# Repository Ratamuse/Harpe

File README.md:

# Harpe anti frelons à pattes jaunes

La construction de cette harpe fait suite à différents essais effectués les années passées. Montage en tubes PVC, armature en bois, bac de noyade. Ces solutions, certes peu chères, ne me satisfaisaient pas. Manque de rigidité, vieillessement prématuré, problème de cours circuits, noyades d'insectes et d'abeilles en pagaille etc etc. 
Ce montage n'est pas "LOW COST" et ne peux rivaliser avec les montages fait à partir de tréteaux, tuyaux de récupération ou autre. C'est une compilation de ce qui existe déjà, avec des améliorations et les plans sont disponibles si vous voulez en construire une.  
Ayant eu des soucis de cours circuits par le passé, j'ai ajouté un microntroleur avec capteur de luminosité et d'humidité afin de couper le montage la nuit et lorsque l'humidité est trop forte. 

Vous trouverez ci dessous les liens pour:

- [Liste du materiel](https://github.com/Ratamuse/Harpe/blob/main/Harpe%20ruches/Materiel/Materiel.md)
- [Fichier .STL pour impression 3D](https://github.com/Ratamuse/Harpe/tree/main/Harpe%20ruches%2FFichiers%203d%20%C3%A0%20imprimer)
- [Aide au montage](https://github.com/Ratamuse/Harpe/blob/main/Harpe%20ruches/Montage/Construction.md)
- [Fichiers nécessaires pour fabriquer le circuit imprimé de la harpe](https://github.com/Ratamuse/Harpe/tree/main/Harpe%20ruches/Fichier%20Kicad)
- [Exemple de montage électrique](https://github.com/Ratamuse/Harpe/blob/main/Harpe%20ruches/Fichier%20Kicad/Harpe_ESP32/PCB.md)
- [Programme pour microcontroleur ESP32](https://github.com/Ratamuse/Harpe/tree/main/Harpe%20ruches/Code%20Arduino)

** Cette harpe vous plait et est efficace. Payez moi un café! ;-) **

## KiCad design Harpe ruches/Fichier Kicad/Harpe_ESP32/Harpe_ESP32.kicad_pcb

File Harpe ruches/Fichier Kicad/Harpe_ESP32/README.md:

## Testboard V2.2 ESP32

## Carte multi-usage basée sur le module ESP-WROOM-32E:

- Connecteur USB-C

- Chargeur solaire MPPT basé sur la puce CN3791:  http://www.consonance-elec.com/pdf/datasheet/DSE-CN3791.pdf

- Connecteur batterie JST-PH 2mm avec protection (surcharge ou décharge profonde)

- Connecteur batterie JST-PH 2mm sans protection (pour batterie déjà protégée)

- Bouton on/off LTC2954 avec interrupt sur µP (On/Off de l'ESP32 et GPIO de l'interrupt utilisable pour des actions): https://www.analog.com/media/en/technical-documentation/data-sheets/2954fb.pdf

- Capteur température/humidité SHT41: https://www.sensirion.com/fileadmin/user_upload/customers/sensirion/Dokumente/2_Humidity_Sensors/Datasheets/Sensirion_Humidity_Sensors_SHT4x_Datasheet.pdf
- 10 optocoupleurs pour interrupteurs à contacts secs (pour domotiser volets roulants, télécommandes diverses) ou au choix 10 GPIO dispo avec au choix alim 3.3V ou "5V" (Vbat (entre 3.2 et 4.2V) ou Vbus (5V)) pour ajouter des modules.

- Chargeur Li-io/Li-Po MCP73831 via port USB-C

- Connecteur JST-PH 2mm (1x4) I2C

- Connecteur JST-PH 2mm (1x4) sur 2 GPIO + choix 3.3V ou 5V

- Connecteur JST-PH 2mm (1x3) sur 1 GPIO (que j'utilise pour piloter des leds neopixel)

Inspiration des travaux de Lilygo, Waveshare, GreatScoot.

Motivation et champs des possibles donnés par P. Demerliac et sa chaine Youtube Cyrob: https://www.youtube.com/channel/UC5QPFDZ3Y4ylkkGJc6Y1OOA  

Initiation à la bricole par P. W. Trainer

Prochaine étape, améliorer le hardaware du GNUVario-E

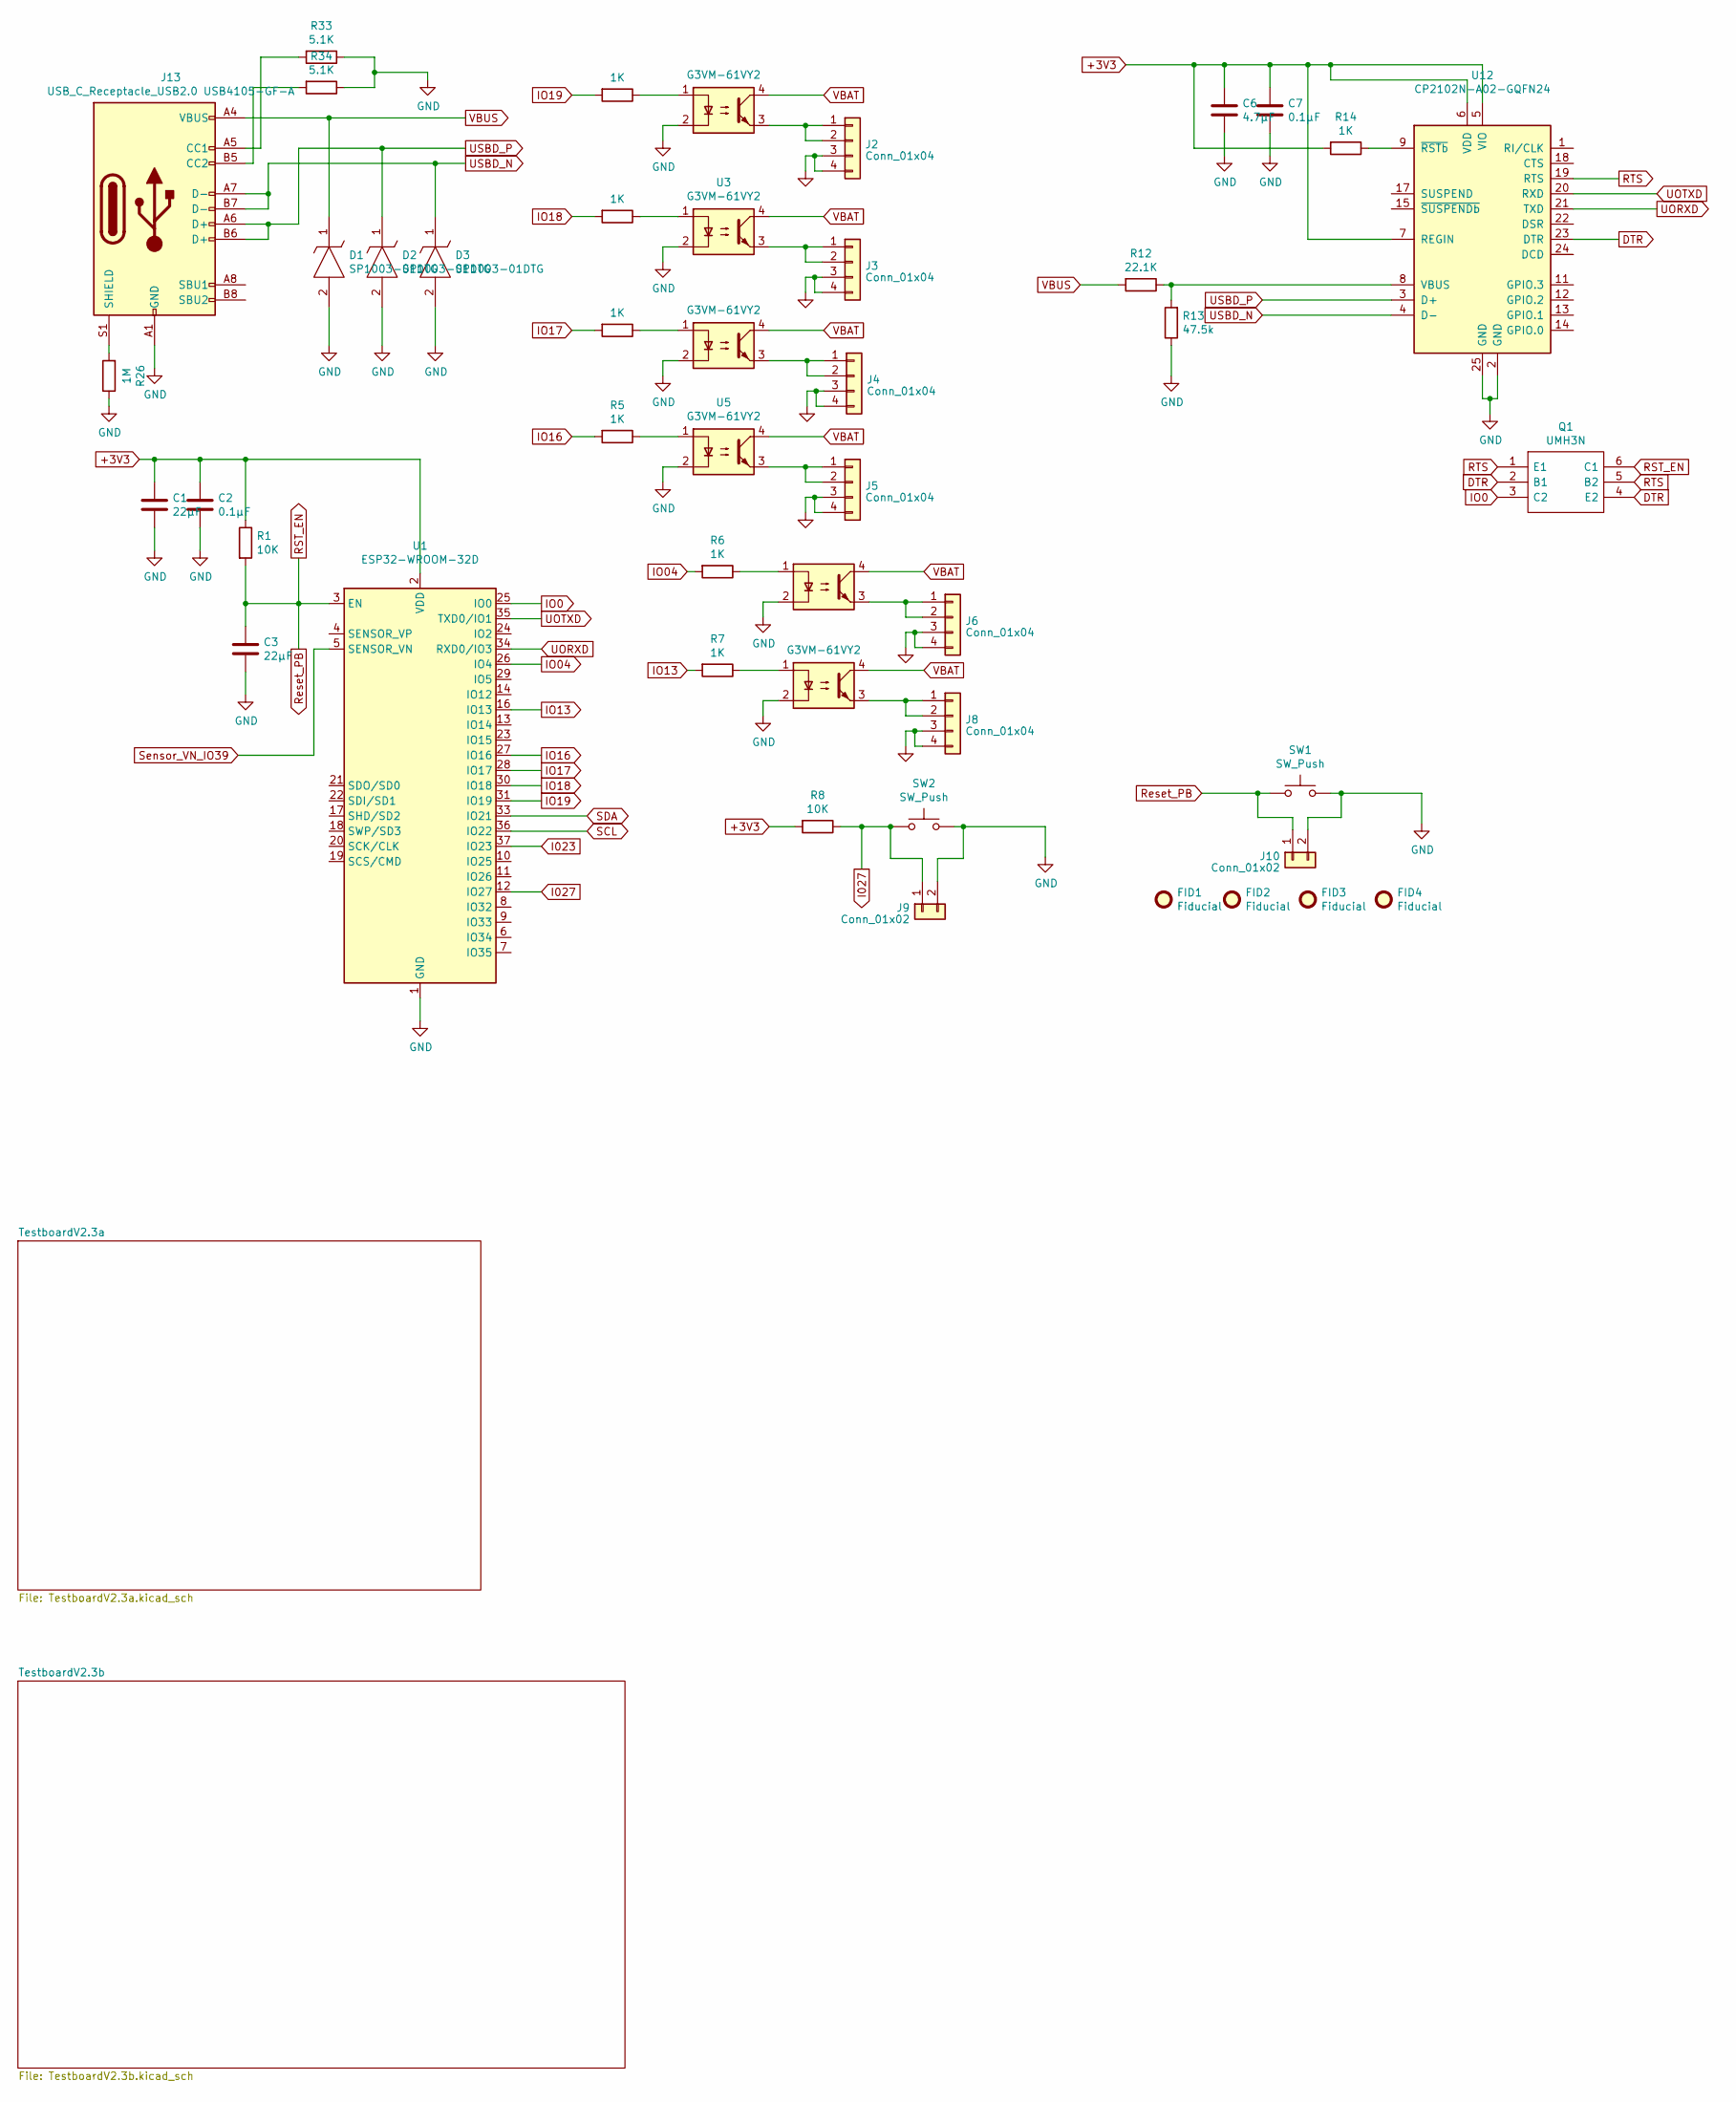
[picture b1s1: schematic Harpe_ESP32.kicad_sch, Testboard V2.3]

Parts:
C1: 22µF; 1190297
C2, C7: 0.1µF; C_0603_1608Metric
C3: 22µF; C_0805_2012Metric
C6: 4.7µF; C_0805_2012Metric
D1, D2, D3: SP1003-01DTG; SODFL1406X65N; Manufacturer_Part_Number SP1003-01DTG; Mouser Part Number 576-SP1003-01DTG
FID1, FID2, FID3, FID4: Fiducial; Fiducial_1.5mm_Mask3mm
J2, J3, J4, J5, J6, J8: Conn_01x04; 1862411
J9, J10: Conn_01x02; JST_PH_B2B-PH-K_1x02_P2.00mm_Vertical
J13: USB_C_Receptacle_USB2.0 USB4105-GF-A; TYPE-C-31-M-12
Q1: UMH3N; SOT-363_SC-70-6; Manufacturer_Part_Number UMH3N
R1, R8: 10K; R_0603_1608Metric
R2, R3, R4, R5, R6, R7, R14: 1K; R_0603_1608Metric
R12: 22.1K; R_0603_1608Metric
R13: 47.5k; R_0603_1608Metric
R26: 1M; R_0603_1608Metric
R33, R34: 5.1K; R_0603_1608Metric
SW1, SW2: SW_Push; PTS636SL43SMTRLFS
U1: ESP32-WROOM-32D; ESP32WROOM32EM113EH2800PH3Q0
U2, U3, U4, U5, U6, U7: G3VM-61VY2; SOP254P700X230-4N
U12: CP2102N-A02-GQFN24; QFN-24-1EP_4x4mm_P0.5mm_EP2.6x2.6mm

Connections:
+3V3: C1.1, C2.1, C6.1, C7.1, R1.1, R8.2, R14.2, U1.2 (VDD), U12.5 (VIO), U12.6 (VDD), U12.7 (REGIN); also elsewhere on the board
DTR: Q1.2 (B1), Q1.4 (E2), U12.23 (DTR)
I023: U1.37 (IO23)
I027: J9.1, R8.1, SW2.1, U1.12 (IO27)
IO0: Q1.3 (C2), U1.25 (IO0)
IO04: R6.2, U1.26 (IO4)
IO13: R7.2, U1.16 (IO13)
IO16: R5.2, U1.27 (IO16)
IO17: R4.2, U1.28 (IO17)
IO18: R3.2, U1.30 (IO18)
IO19: R2.2, U1.31 (IO19)
unnamed: J2.1, J2.2, U2.3
unnamed: J3.1, J3.2, U3.3
unnamed: J4.1, J4.2, U4.3
unnamed: J5.1, J5.2, U5.3
unnamed: J6.1, J6.2, U6.3
unnamed: J13.A5 (CC1), R33.2
unnamed: J13.B5 (CC2), R34.2
unnamed: J13.S1 (SHIELD), R26.2
unnamed: R2.1, U2.1
unnamed: R3.1, U3.1
unnamed: R4.1, U4.1
unnamed: R5.1, U5.1
unnamed: R6.1, U6.1
unnamed: R7.1, U7.1
unnamed: R12.1, R13.2, U12.8 (VBUS)
unnamed: R14.1, U12.9 (~RSTb)
RST_EN: C3.1, J10.1, Q1.6 (C1), R1.2, SW1.1, U1.3 (EN)
RTS: Q1.1 (E1), Q1.5 (B2), U12.19 (RTS)
SCL: U1.36 (IO22); also elsewhere on the board
SDA: U1.33 (IO21); also elsewhere on the board
Sensor_VN_IO39: U1.5 (SENSOR_VN)
UORXD: U1.34 (RXD0/IO3), U12.21 (TXD)
UOTXD: U1.35 (TXD0/IO1), U12.20 (RXD)
USBD_N: D3.1, J13.A7 (D-), J13.B7 (D-), U12.4 (D-)
USBD_P: D2.1, J13.A6 (D+), J13.B6 (D+), U12.3 (D+)
VBUS: D1.1, J13.A4 (VBUS), J13.A9 (VBUS), J13.B4 (VBUS), J13.B9 (VBUS), R12.2; also elsewhere on the board

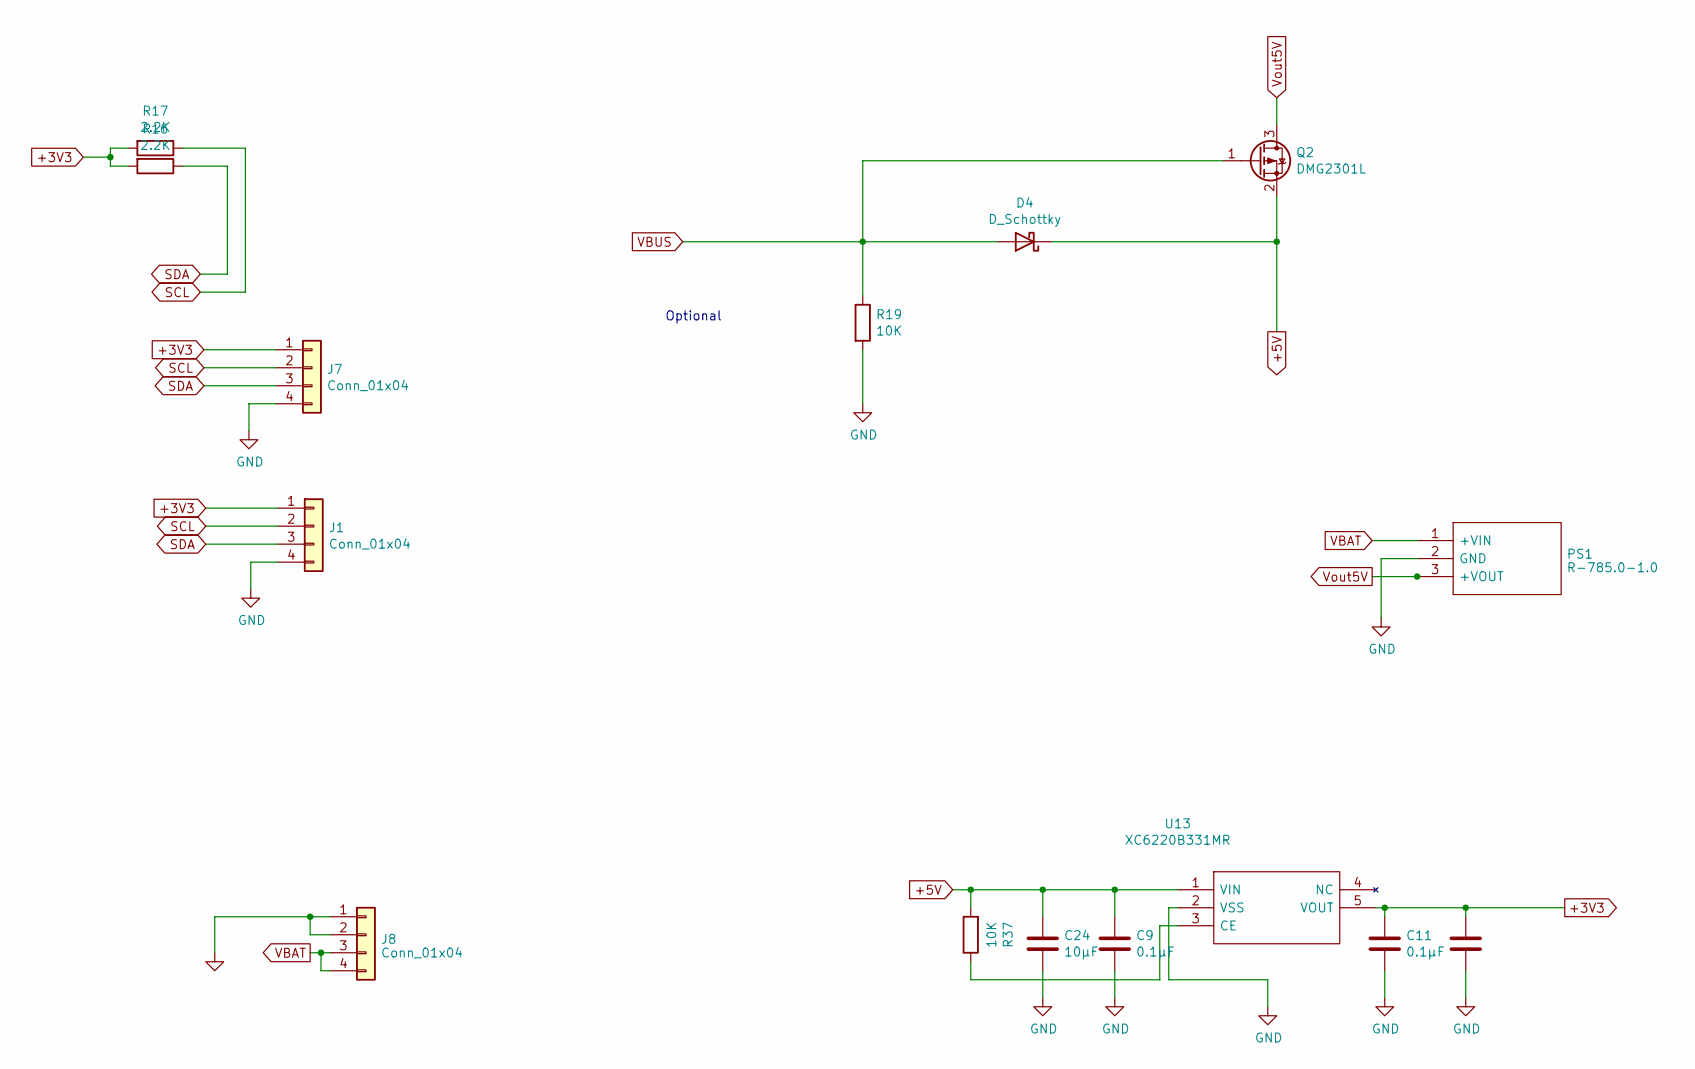
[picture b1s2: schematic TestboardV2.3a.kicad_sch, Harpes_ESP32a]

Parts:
C9, C11: 0.1µF; C_0603_1608Metric
C24, C25: 10µF; C_0805_2012Metric
D4: D_Schottky; D_SOD-323
J1, J7: Conn_01x04; 1989764
J8: Conn_01x04; 1862411
PS1: R-785.0-1.0; R785010; Mouser Part Number 919-R-785.0-1.0
Q2: DMG2301L; SOT-23
R16, R17: 2.2K; R_0603_1608Metric
R19, R37: 10K; R_0603_1608Metric
U13: XC6220B331MR; SOT-23-5

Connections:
+3V3: C11.1, C25.1, J1.1, J7.1, R16.2, R17.2, U13.5 (VOUT); also elsewhere on the board
+5V: C9.1, C24.1, D4.1 (K), Q2.2 (S), R37.2, U13.1 (VIN)
unnamed: R37.1, U13.3 (CE)
SCL: J1.2, J7.2, R17.1; also elsewhere on the board
SDA: J1.3, J7.3, R16.1; also elsewhere on the board
VBUS: D4.2 (A), Q2.1 (G), R19.1; also elsewhere on the board
Vout5V: PS1.3 (+VOUT), Q2.3 (D)

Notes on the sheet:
Optional

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
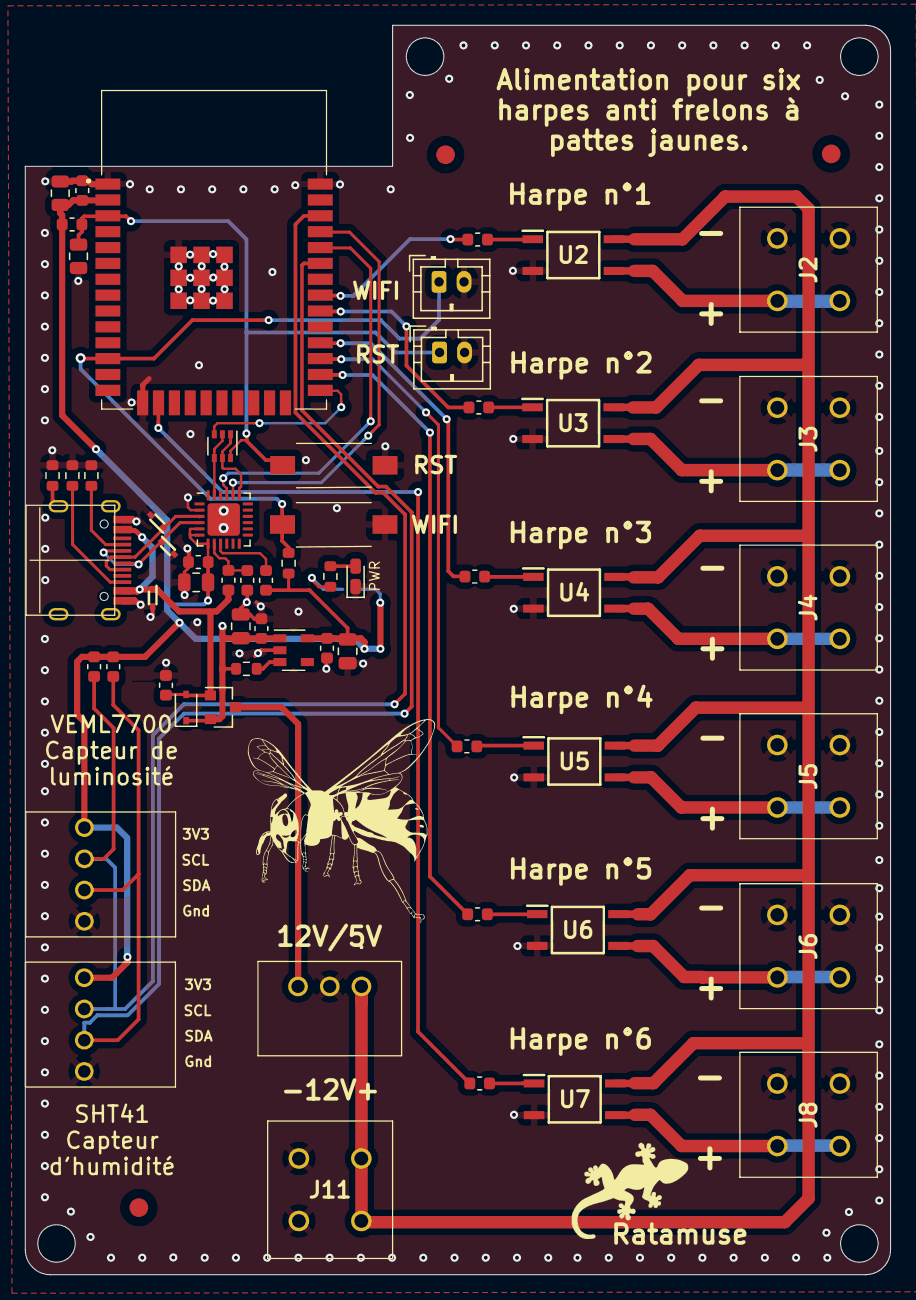
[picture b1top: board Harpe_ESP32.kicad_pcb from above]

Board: 2 copper layers, 69.3 x 100.0 mm, 63 parts (1 on the bottom side), 43 nets.

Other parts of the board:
D15: LED Green; LED_0603_1608Metric_Castellated
J11: Conn_01x04; 1862411
JP21: SolderJumper_2_Open; SolderJumper-2_P1.3mm_Open_RoundedPad1.0x1.5mm
R29: 10K; R_0603_1608Metric

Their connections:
+3V3: JP21.1; also elsewhere on the board
unnamed: D15.2, R29.1
unnamed: JP21.2, R29.2

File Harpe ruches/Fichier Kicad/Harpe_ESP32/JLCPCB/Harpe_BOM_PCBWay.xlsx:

|  |  | xxxx xxxx xxxxx xxPCS BOM (Sample Bill of Materials)
Item # | *Designator | *Qty | Manufacturer | *Mfg Part # | Description / Value | *Package/Footprint | Type | Your Instructions / Notes
1 | C1,C3 | 2 | Murata | GRM219R61C226ME15L | 16V 22uF X5R ±20% 0805 Multilayer Ceramic Capacitors MLCC | C_0805_2012Metric
2 | C2,C7,C9,C11 | 4 | Murata | GCJ188R71C104KA01D | MLCC - CMS 0.1 uF 16 VDC 10% 0603 X7R | C_0603_1608Metric
3 | C6 | 1 | Murata | GCM21BR71C475KA73L | MLCC - CMS 4.7 uF 16 VDC 10% 0805 X7R | C_0805_2012Metric
4 | R1,R19,R29,R8,R37 | 5 | YAGEO | RT0603BRD0710KL | 100mW Thin Film Resistor ±25ppm/℃ ±0.1% 10kΩ 0603 Chip Resistor - Surface Mount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 | R_0603_1608Metric
5 | R2,R3,R4,R5,R6,R7,R14 | 7 | YAGEO | RT0603BRD071KL | 100mW Thin Film Resistor ±25ppm/℃ ±0.1% 1kΩ 0603 Chip Resistor - Surface Mount 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 | R_0603_1608Metric
6 | R12 | 1 | YAGEO | RT0603BRD0722K1L | 100mW Thin Film Resistor ±25ppm/℃ ±0.1% 22.1kΩ 0603 Chip Resistor - Surface Mou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 | R_0603_1608Metric
7 | R13 | 1 | YAGEO | RT0603BRD0747K5L | 100mW Thin Film Resistor ±25ppm/℃ ±0.1% 47.5kΩ 0603 Chip Resistor - Surface Mou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 | R_0603_1608Metric
8 | U1 | 1 | Espressif | ESP32-WROOM-32E-N4 | ESP32-WROOM-32E-N4 | SMD,18x25.5mm
9 | U2,U3,U4,U5,U6,U7 | 6 | Omron Electronics | G3VM-61VY2 |  | SOP254P960X420-4N
10 | U12 | 1 | SILICON LABS | CP2102N-A02-GQFN24R | USB转UART UART QFN-24-EP(4x4) USB ICs ROHS | QFN-24-1EP_4x4mm_P0.5mm_EP2.6x2.6mm
11 | U13 | 1 | Torex Semicon | XC6220B331MR-G |  | SOT-23-5
14 | R16,R17 | 2 | YAGEO | AT0603BRD072K2L | 100mW Thin Film Resistor ±25ppm/℃ ±0.1% 2.2kΩ 0603 Chip Resistor - Surface Moun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 | R_0603_1608Metric
15 | D4 | 1 | STMicroelectronics | BAT20JFILM |  | D_SOD-323
16 | Q1 | 1 | ROHM Semicon | UMH3NTN | 100@1mA,5V 2 NPN - Pre-Biased 150mW 100mA 50V SOT-363 | SOT-363_SC-70-6
17 | Q2 | 1 | Diodes Incorporated | DMG2301L-7 | 20V 3A 1.5W 120mΩ@4.5V,2.8A 1.2V@250uA P Channel SOT-23 MOSFETs ROHS | SOT-23
18 | D1,D2,D3 | 3 | Littelfuse | SP1003-01DTG | 7A@8/20us 12V@(Typ) 6V Unidirectional 5V@Max SOD-723 TVS ROHS | SODFL1406X65N
19 | J13 | 1 | GCT | USB4105-GF-A | Connectors USB USB Type C,2.0, Rec,SMT, 0.95mmTH Shell Stakes,G/F,RA,Top Mnt,T&R | USB_C_Receptacle_USB2.0 USB4105-GF-A
20 | R26 | 1 | YAGEO | RT0603FRE071ML | 100mW Thin Film Resistor ±50ppm/℃ ±1% 1MΩ 0603 Chip Resistor - Surface Mount RO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 | R_0603_1608Metric
21 | R33,R34 | 2 | YAGEO | RT0603BRD075K1L | 100mW Thin Film Resistor ±25ppm/℃ ±0.1% 5.1kΩ 0603 | R_0603_1608Metric
22 | D15 | 1 | XINGLIGHT | XL-1608VRC-06 | 90mcd 红色透镜 615nm~630nm 正贴 Red 120° 75mW 0603 Light Emitting Diodes (LED) ROHS | LED_0603_1608Metric_Castellated
23 | C24,C25 | 2 | Murata | GRM21BR61C106KE15K | 16V 10uF X5R ±10% 0805 Multilayer Ceramic Capacitors MLCC - SMD/SMT ROHS | C_0805_2012Metric
Need a quick and accurante quote? Need an efficient production? Please read SMT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
Click for Instructions on How to Create a BOM

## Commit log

2023-09-23 Revert "Auxiliary commit to revert individual files from c0a4d603793bf890a5a828aa582f61ec66cf159f"
    This reverts commit cd00cefafacd54ed8f00dbb090a7ca136d19df84.
2023-09-28 Update PCB
2023-09-28 Revert "Update PCB"
    This reverts commit 88c6fc853c4fb05f29f730f761ab4a511938047f.
2023-10-05 code arduino
2023-11-01 Mise à jour
2023-11-24 code
2023-12-01 Mise à jour du code
2023-12-11 code & image update
2023-12-11 construction updated
2023-12-12 pcb updated
2023-12-13 dessin update
2024-07-20 pcb bas update
